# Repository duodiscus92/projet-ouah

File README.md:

# projet-ouah
You will find here, all requested files to buid the ouah! project
1) Publication with detailed instructions to build the project.
  YOU MUST READ IT before going futher
  The OUAH! board contains an integrated power supply powered by 220 v.
    Precautions for use are therefore necessary to avoid any electrocution.
    Please, see the recommendations made in this publication.
    It is the responsibility of readers wishing to carry out the Ouah! to take all the necessary precautions,
     the author can in no way be held responsible for the consequences of an electric shock.
3) Files to build the DCF77 clock :
- Kicad files including schematic and printed circuit board
- VHDL sources and and bin file to be uploaded to the Upduino board
3) Files to build the DCF77 simulator
- souces C files for Raspbery Pi (A Zero W is enough to execute the simulator)
- source C files for Pico W (only requested if you decide to integer the simulator into the clock)
I recommend to visit periodically the gihub of this project to get the last updates if any.

I can provide ligth support and collect remarks and suggestions on this mail:
mailto:support.ouah@orange.fr

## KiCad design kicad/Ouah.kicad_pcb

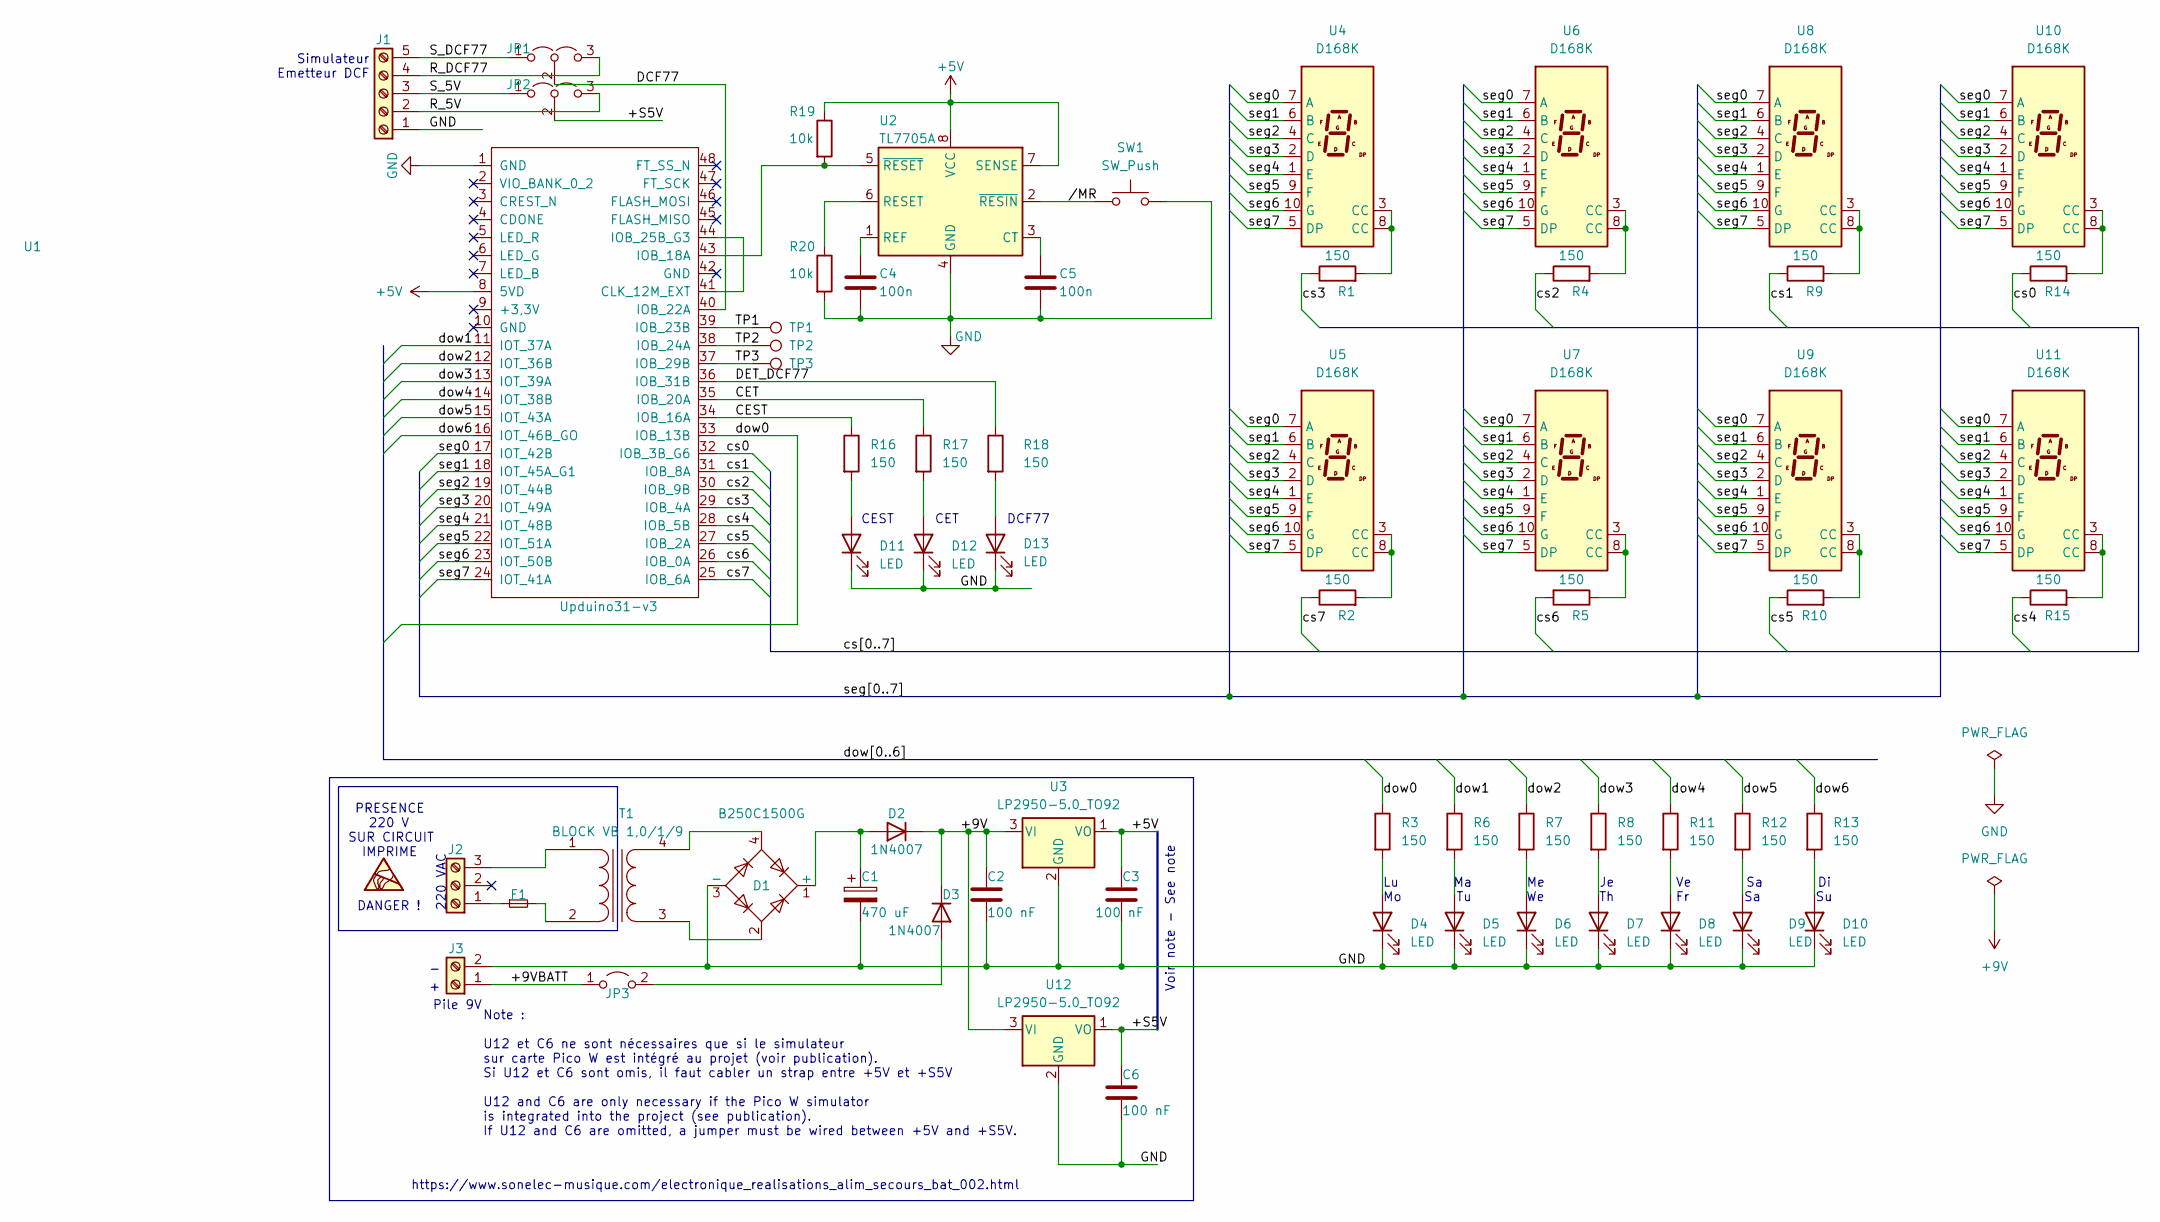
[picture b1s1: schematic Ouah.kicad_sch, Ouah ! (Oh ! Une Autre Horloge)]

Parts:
C1: 470 uF; CP_Radial_D10.0mm_P5.00mm
C2, C3, C6: 100 nF; C_Rect_L7.2mm_W2.5mm_P5.00mm_FKS2_FKP2_MKS2_MKP2
C4, C5: 100n; C_Rect_L7.2mm_W2.5mm_P5.00mm_FKS2_FKP2_MKS2_MKP2
D1: B250C1500G; Diode_Bridge_Round_D9.8mm
D2, D3: 1N4007; D_DO-41_SOD81_P10.16mm_Horizontal
D4, D5, D6, D7, D8, D9, D10, D11, D12, D13: LED; LED_D5.0mm
F1: Fuse_Small; Fuseholder_TR5_Littelfuse_No560_No460
J1: Screw_Terminal_01x05; TerminalBlock_bornier-5_P5.08mm
J2: Screw_Terminal_01x03; TerminalBlock_bornier-3_P5.08mm
J3: Screw_Terminal_01x02; TerminalBlock_bornier-2_P5.08mm
JP1, JP2: Jumper_3_Open; PinHeader_1x03_P2.54mm_Vertical
JP3: Jumper_2_Open; PinHeader_1x02_P2.54mm_Vertical
R1, R2, R4, R5, R9, R10, R14, R15: 150; R_Axial_DIN0207_L6.3mm_D2.5mm_P7.62mm_Horizontal
R3, R6, R7, R8, R11, R12, R13, R16, R17, R18: 150; R_Axial_DIN0207_L6.3mm_D2.5mm_P2.54mm_Vertical
R19, R20: 10k; R_Axial_DIN0207_L6.3mm_D2.5mm_P2.54mm_Vertical
SW1: SW_Push; SW_PUSH_6mm
T1: BLOCK VB 1,0/1/9; Transformer_CHK_EI30-2VA_1xSec_RevEHR
TP1, TP2, TP3: TestPoint; TestPoint_THTPad_3.0x3.0mm_Drill1.5mm
U1: Upduino31-v3; DIP-48_W17.78mm_LongPads
U2: TL7705A; DIP-8_W7.62mm_Socket_LongPads
U3, U12: LP2950-5.0_TO92; TO-92_Inline_Wide
U4, U5, U6, U7, U8, U9, U10, U11: D168K; D1X8K_RevEHR

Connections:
+5V: C3.2, R19.1, U1.8 (5VD), U2.7 (SENSE), U2.8 (VCC), U3.1 (VO)
+9V: C2.2, D2.1 (K), D3.1 (K), U3.3 (VI), U12.3 (VI)
/+9VBATT: J3.1, JP3.1 (A)
/+S5V: C6.2, JP2.2 (C), U12.1 (VO)
/CEST: R16.1, U1.34 (IOB_16A)
/CET: R17.1, U1.35 (IOB_20A)
/DCF77: JP1.2 (C), U1.40 (IOB_22A)
/DET_DCF77: R18.1, U1.36 (IOB_31B)
/R_5V: J1.2, JP2.3 (B)
/R_DCF77: J1.4, JP1.3 (B)
/S_5V: J1.3, JP2.1 (A)
/S_DCF77: J1.5, JP1.1 (A)
/TP1: TP1.1, U1.39 (IOB_23B)
/TP2: TP2.1, U1.38 (IOB_24A)
/TP3: TP3.1, U1.37 (IOB_29B)
/cs0: R14.1, U1.32 (IOB_3B_G6)
/cs1: R9.1, U1.31 (IOB_8A)
/cs2: R4.1, U1.30 (IOB_9B)
/cs3: R1.1, U1.29 (IOB_4A)
/cs4: R15.1, U1.28 (IOB_5B)
/cs5: R10.1, U1.27 (IOB_2A)
/cs6: R5.2, U1.26 (IOB_0A)
/cs7: R2.1, U1.25 (IOB_6A)
/dow0: R3.1, U1.33 (IOB_13B)
/dow1: R6.1, U1.11 (IOT_37A)
/dow2: R7.1, U1.12 (IOT_36B)
/dow3: R8.1, U1.13 (IOT_39A)
/dow4: R11.1, U1.14 (IOT_38B)
/dow5: R12.1, U1.15 (IOT_43A)
/dow6: R13.1, U1.16 (IOT_46B_GO)
/seg0: U1.17 (IOT_42B), U4.7 (A), U5.7 (A), U6.7 (A), U7.7 (A), U8.7 (A), U9.7 (A), U10.7 (A), U11.7 (A)
/seg1: U1.18 (IOT_45A_G1), U4.6 (B), U5.6 (B), U6.6 (B), U7.6 (B), U8.6 (B), U9.6 (B), U10.6 (B), U11.6 (B)
/seg2: U1.19 (IOT_44B), U4.4 (C), U5.4 (C), U6.4 (C), U7.4 (C), U8.4 (C), U9.4 (C), U10.4 (C), U11.4 (C)
/seg3: U1.20 (IOT_49A), U4.2 (D), U5.2 (D), U6.2 (D), U7.2 (D), U8.2 (D), U9.2 (D), U10.2 (D), U11.2 (D)
/seg4: U1.21 (IOT_48B), U4.1 (E), U5.1 (E), U6.1 (E), U7.1 (E), U8.1 (E), U9.1 (E), U10.1 (E), U11.1 (E)
/seg5: U1.22 (IOT_51A), U4.9 (F), U5.9 (F), U6.9 (F), U7.9 (F), U8.9 (F), U9.9 (F), U10.9 (F), U11.9 (F)
/seg6: U1.23 (IOT_50B), U4.10 (G), U5.10 (G), U6.10 (G), U7.10 (G), U8.10 (G), U9.10 (G), U10.10 (G), U11.10 (G)
/seg7: U1.24 (IOT_41A), U4.5 (DP), U5.5 (DP), U6.5 (DP), U7.5 (DP), U8.5 (DP), U9.5 (DP), U10.5 (DP), U11.5 (DP)
//MR: SW1.1, U2.2 (~RESIN)
GND: C1.2, C2.1, C3.1, C4.2, C5.2, C6.1, D1.3 (-), D4.1 (K), D5.1 (K), D6.1 (K), D7.1 (K), D8.1 (K), D9.1 (K), D10.1 (K), D11.1 (K), D12.1 (K), D13.1 (K), J1.1, J3.2, R20.2, SW1.2, U1.1 (GND), U2.4 (GND), U3.2 (GND), U12.2 (GND)
unnamed: C1.1, D1.1 (+), D2.2 (A)
unnamed: C4.1, U2.1 (REF)
unnamed: C5.1, U2.3 (CT)
unnamed: D1.2, T1.3 (SA)
unnamed: D1.4, T1.4 (SB)
unnamed: D3.2 (A), JP3.2 (B)
unnamed: D4.2 (A), R3.2
unnamed: D5.2 (A), R6.2
unnamed: D6.2 (A), R7.2
unnamed: D7.2 (A), R8.2
unnamed: D8.2 (A), R11.2
unnamed: D9.2 (A), R12.2
unnamed: D10.2 (A), R13.2
unnamed: D11.2 (A), R16.2
unnamed: D12.2 (A), R17.2
unnamed: D13.2 (A), R18.2
unnamed: F1.1, J2.1
unnamed: F1.2, T1.2 (AB)
unnamed: J2.3, T1.1 (AA)
unnamed: R1.2, U4.3 (CC), U4.8 (CC)
unnamed: R2.2, U5.3 (CC), U5.8 (CC)
unnamed: R4.2, U6.3 (CC), U6.8 (CC)
unnamed: R5.1, U7.3 (CC), U7.8 (CC)
unnamed: R9.2, U8.3 (CC), U8.8 (CC)
unnamed: R10.2, U9.3 (CC), U9.8 (CC)
unnamed: R14.2, U10.3 (CC), U10.8 (CC)
unnamed: R15.2, U11.3 (CC), U11.8 (CC)
unnamed: R19.2, U1.43 (IOB_18A), U2.5 (~RESET)
unnamed: R20.1, U2.6 (RESET)
unnamed: U1.41 (CLK_12M_EXT), U1.44 (IOB_25B_G3)

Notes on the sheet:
Note : U12 et C6 ne sont nécessaires que si le simulateur sur carte Pico W est intégré au projet (voir publication). Si U12 et C6 sont omis, il faut cabler un strap entre +5V et +S5V U12 and C6 are only necessary if the Pico W simulator is integrated into the project (see publication). If U12 and C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
Voir note - See note
Simulateur Emetteur DCF
DANGER !
PRESENCE 220 V SUR CIRCUIT IMPRIME
https://www.sonelec-musique.com/electronique_realisations_alim_secours_bat_002.html
Pile 9V
220 VAC
CEST CET DCF77
Lu Ma Me Je Ve Sa Di Mo Tu We Th Fr Sa Su

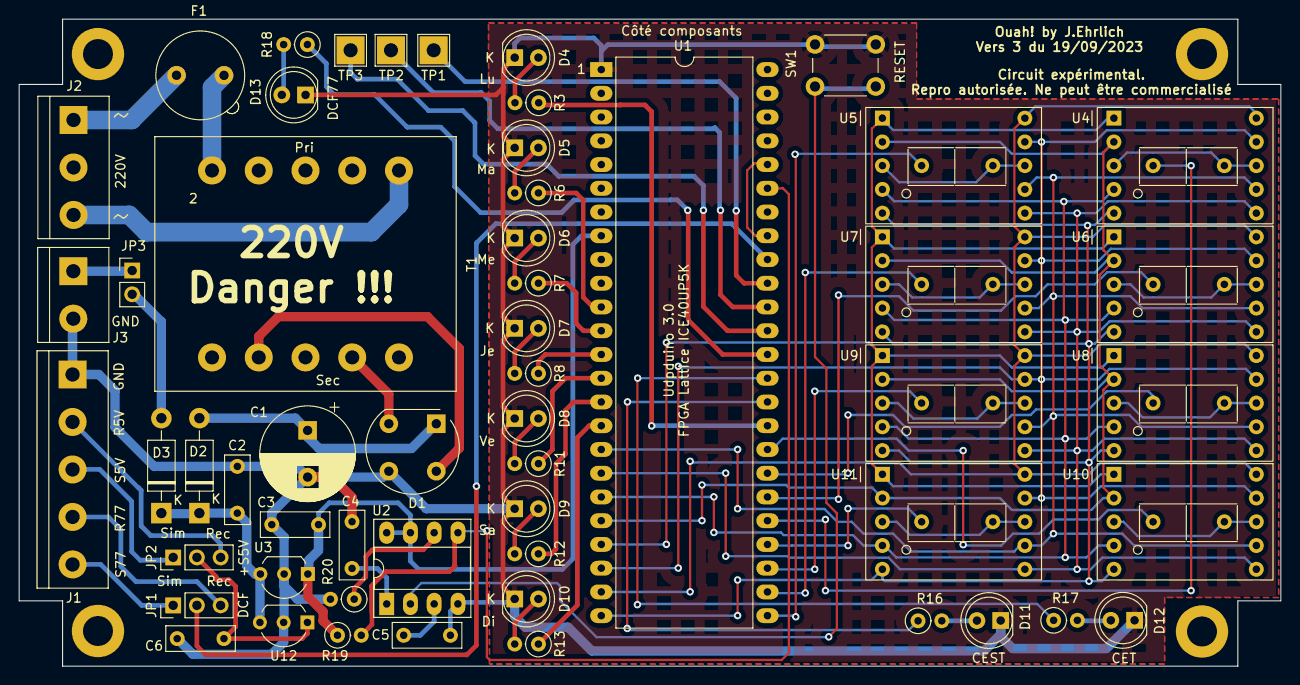
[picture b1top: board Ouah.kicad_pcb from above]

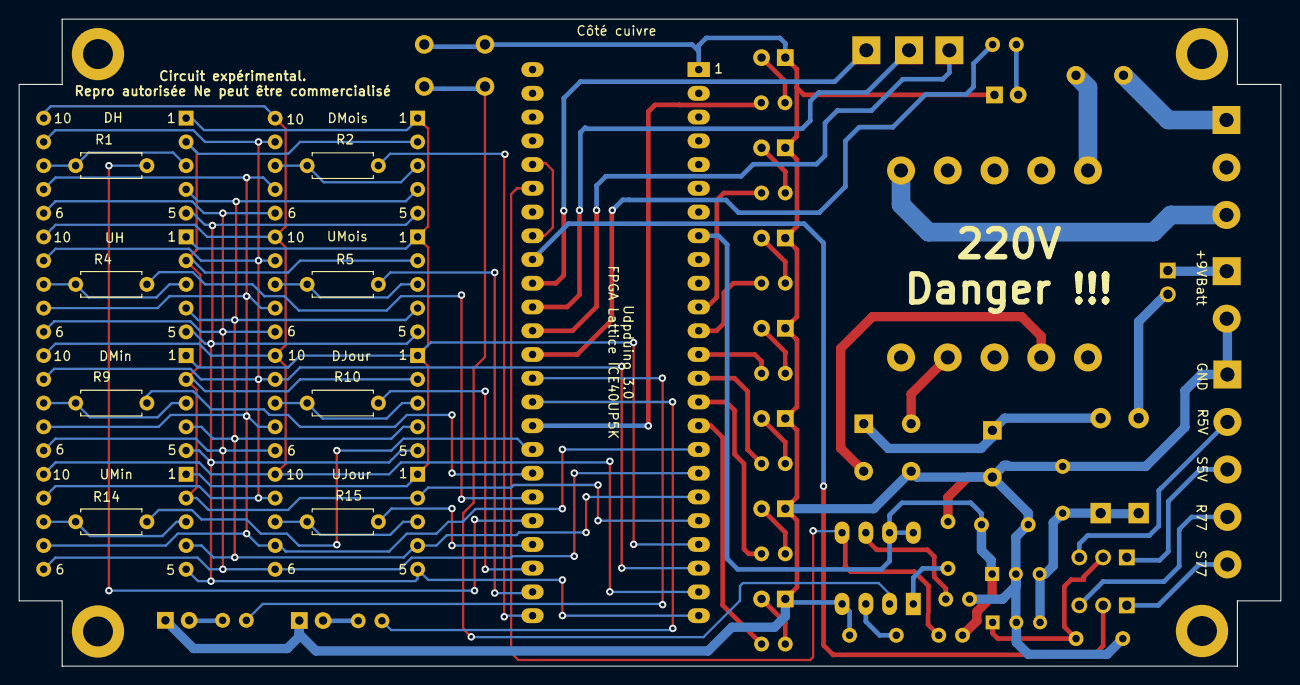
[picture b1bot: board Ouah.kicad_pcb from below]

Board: 2 copper layers, 135.0 x 69.2 mm, 66 parts (8 on the bottom side), 70 nets.

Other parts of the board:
1, 2, 3: (no value)

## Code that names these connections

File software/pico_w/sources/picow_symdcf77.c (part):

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#define NTP_TEST_TIME (30 * 1000)
#define NTP_RESEND_TIME (10 * 1000)

#define GPIO_DCF77 28
#define HIGH 1
#define LOW 0
// overide SSID and PASSWORD definition in CMakeLists.txt
//#define WIFI_SSID "XXXXXXXX"
//#define WIFI_PASSWORD "XXXXXXXX"
// Time zone for Paris (must be replaced by yours)
#define TIME_ZONE "CET-1CEST-2,M3.5.0/2,M10.5.0/3"


// Sstruct for rtc
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    .sec   = 0
};

static int cet_cest_flag = 0; // >0 means CEST, 0 means CET
static int header[] = {
   1,		//start minutes (always at 1)
   1,1,1,1,1,1,1,1,1,1,1,1,1,1,1,
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void send_one(void)
{
   cyw43_arch_gpio_put(CYW43_WL_GPIO_LED_PIN, HIGH);
   gpio_put(GPIO_DCF77, HIGH);
   busy_wait_ms(200);
   cyw43_arch_gpio_put(CYW43_WL_GPIO_LED_PIN, LOW);
   gpio_put(GPIO_DCF77, LOW);
   busy_wait_ms(800);
   printf("1");  fflush(stdout);
}
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void send_zero(void)
{
   cyw43_arch_gpio_put(CYW43_WL_GPIO_LED_PIN, HIGH);
   gpio_put(GPIO_DCF77, HIGH);
   busy_wait_ms(100);
   cyw43_arch_gpio_put(CYW43_WL_GPIO_LED_PIN, LOW);
   gpio_put(GPIO_DCF77, LOW);
    busy_wait_ms(900);
   printf("0");  fflush(stdout);
}
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void send_nothing(void)
{
   cyw43_arch_gpio_put(CYW43_WL_GPIO_LED_PIN, LOW);
   gpio_put(GPIO_DCF77, LOW);
   busy_wait_ms(1000);
   printf("X");  fflush(stdout);
}
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        return 1;
    }

    // intialize GPIO_DCF77 and set it as output
    gpio_init(GPIO_DCF77);
    gpio_set_dir(GPIO_DCF77, GPIO_OUT);
 
    cyw43_arch_enable_sta_mode();

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
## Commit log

2023-11-12 added readme in pico_w directory
2023-11-18 adding elektor teaser and updating README

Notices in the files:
software/pico_w/sources/picow_symdcf77.c:
Copyright (c) 2022 Raspberry Pi (Trading) Ltd.
SPDX-License-Identifier: BSD-3-Clause
